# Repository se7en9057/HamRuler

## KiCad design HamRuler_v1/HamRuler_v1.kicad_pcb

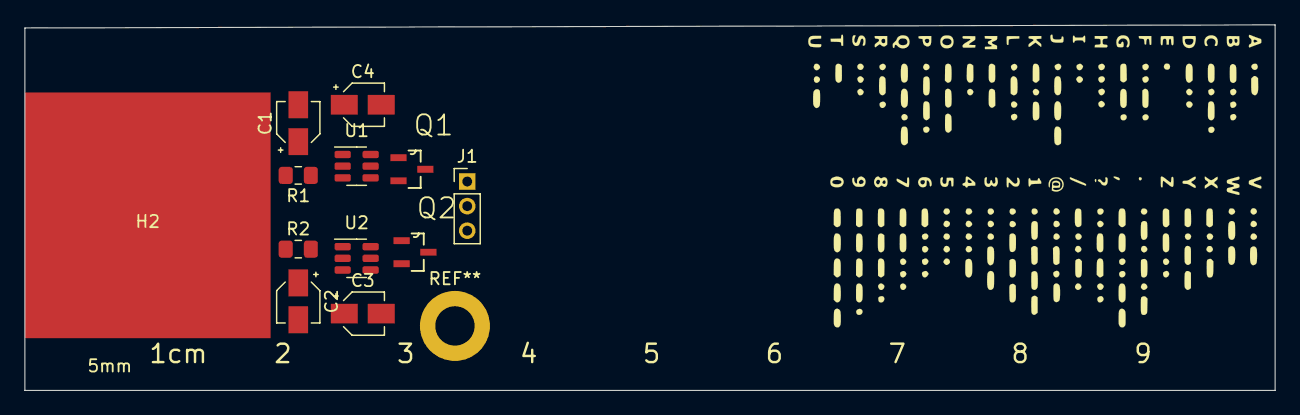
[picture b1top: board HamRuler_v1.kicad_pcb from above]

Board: 2 copper layers, 101.8 x 29.8 mm, 13 parts (1 on the bottom side), 8 nets, no tracks yet.

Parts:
C1, C2, C3, C4: CAP; CP_Elec_3x5.3
H1, H2: MountingHole_Pad; Large Pad
J1: Conn_01x03; PinHeader_1x03_P2.00mm_Vertical
Q1, Q2: BUK7M9R9-60EX; SOT95P240X112-3N
R1, R2: R; R_0805_2012Metric_Pad1.15x1.40mm_HandSolder
U1, U2: AT42QT1011-TSHR; SOT-23-6

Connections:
GND: C3.1, C4.1, J1.2, Q1.1, Q1.2, Q1.3, Q2.1, Q2.2, Q2.3, U1.2, U2.2
unnamed: C1.1, R1.1, U1.3
unnamed: C1.2, U1.4
unnamed: C2.1, R2.1, U2.3
unnamed: C2.2, U2.4
unnamed: H1.1, R1.2
unnamed: H2.1, R2.2
VCC: C3.2, C4.2, U1.5, U1.6, U2.5, U2.6

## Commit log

2022-08-25 initial schematic
2022-08-26 nightly
2022-08-26 move img
2023-05-19 updated kicad version
